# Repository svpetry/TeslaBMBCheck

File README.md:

# TeslaBMBCheck
Simple device that reads the voltage levels and temperatures from a Tesla Model S BMB board. It also supports balancing and clearing faults.

## Module Locations

## BMB Components

For each brick the BMB has a group of identical SMD components to read the voltage levels and do balancing. The elements in the topmost rectangle have already been replaced and re-sealed with epoxy.

## BMB Single Group For A Brick

The components here often have corrosion damage.

## BMB Resistor And Capacitor Values

These are the values I measured.

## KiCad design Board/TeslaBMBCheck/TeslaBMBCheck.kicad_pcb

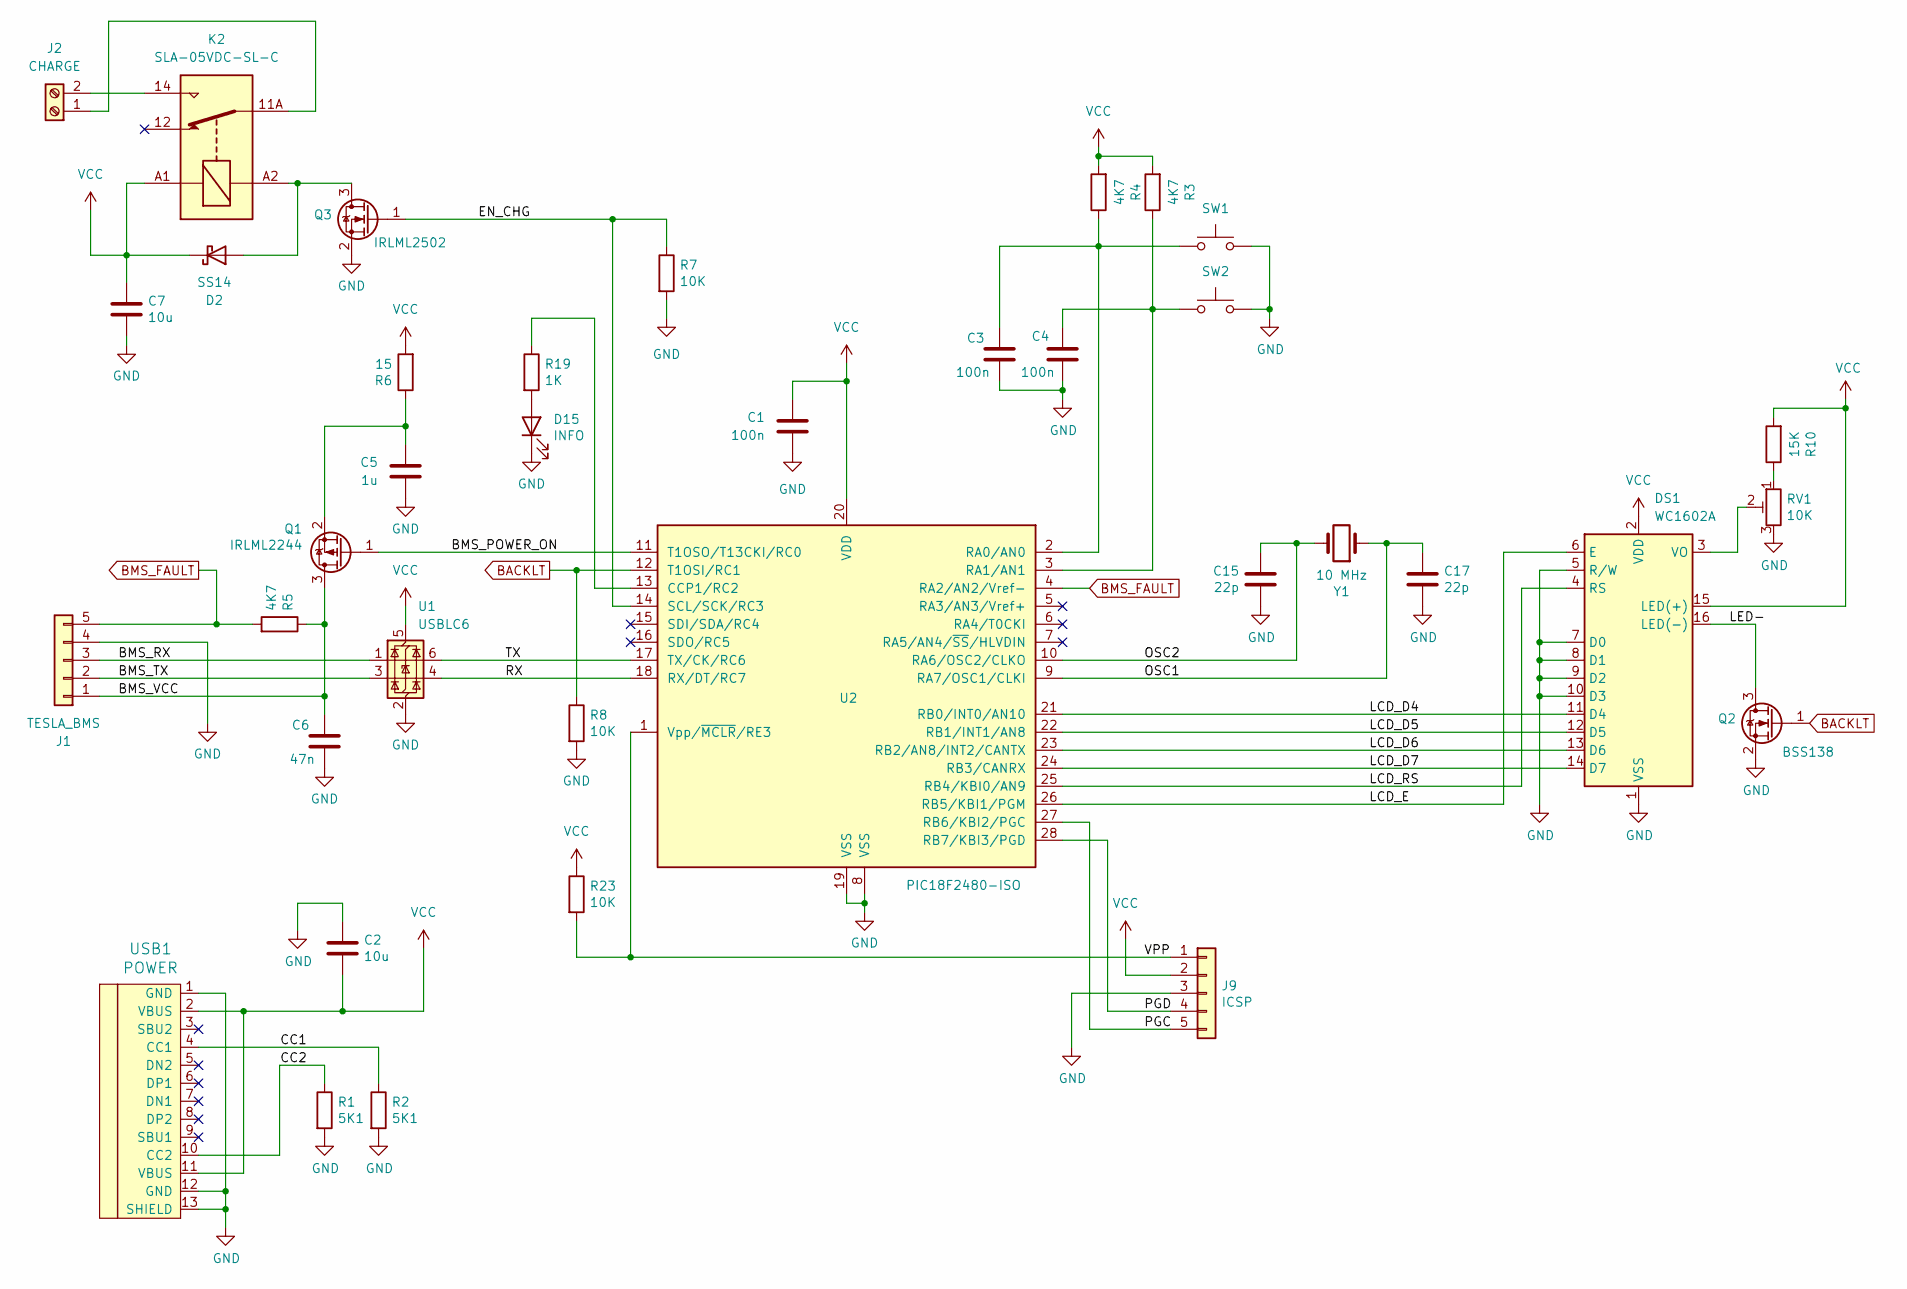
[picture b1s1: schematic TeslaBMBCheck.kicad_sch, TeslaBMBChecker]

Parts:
C1, C3, C4: 100n; C_0805_2012Metric
C2, C7: 10u; C_1206_3216Metric
C5: 1u; C_0805_2012Metric
C6: 47n; C_0805_2012Metric
C15, C17: 22p; C_0805_2012Metric
D2: SS14; D_SMA
D15: INFO; LED_0805_2012Metric
DS1: WC1602A; LCD-20x4
J1: TESLA_BMS; Molex_Mini-Fit_Jr_5566-10A_1x05_P4.20mm_Vertical
J2: CHARGE; KF7.62_2P
J9: ICSP; PinHeader_1x05_P2.54mm_Vertical
K2: SLA-05VDC-SL-C; Relay_SPDT_RAYEX-L90
Q1: IRLML2244; SOT-23
Q2: BSS138; SOT-23
Q3: IRLML2502; SOT-23
R1, R2: 5K1; R_0805_2012Metric
R3, R4, R5: 4K7; R_0805_2012Metric
R6: 15; R_0805_2012Metric
R7, R8, R23: 10K; R_0805_2012Metric
R10: 15K; R_0805_2012Metric
R19: 1K; R_0805_2012Metric
RV1: 10K; Potentiometer_Bourns_TC33X_Vertical
SW1, SW2: SW_SPST_CK_RS282G05A3
U1: USBLC6; SOT-23-6
U2: PIC18F2480-ISO; SOIC-28W_7.5x17.9mm_P1.27mm
USB1: POWER; HRO-TYPE-C-31-M-12
Y1: 10 MHz; Crystal_SMD_HC49-SD

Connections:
/BMS_POWER_ON: Q1.1 (G), U2.11 (T1OSO/T13CKI/RC0)
/BMS_RX: J1.3, U1.1 (I/O1)
/BMS_TX: J1.2, U1.3 (I/O2)
/BMS_VCC: C6.1, J1.1, Q1.3 (D), R5.1
/CC1: R2.1, USB1.4 (CC1)
/CC2: R1.1, USB1.10 (CC2)
/EN_CHG: Q3.1 (G), R7.1, U2.14 (SCL/SCK/RC3)
/LCD_D4: DS1.11 (D4), U2.21 (RB0/INT0/AN10)
/LCD_D5: DS1.12 (D5), U2.22 (RB1/INT1/AN8)
/LCD_D6: DS1.13 (D6), U2.23 (RB2/AN8/INT2/CANTX)
/LCD_D7: DS1.14 (D7), U2.24 (RB3/CANRX)
/LCD_E: DS1.6 (E), U2.26 (RB5/KBI1/PGM)
/LCD_RS: DS1.4 (RS), U2.25 (RB4/KBI0/AN9)
/LED-: DS1.16 (LED(-)), Q2.3 (D)
/OSC1: C17.1, U2.9 (RA7/OSC1/CLKI), Y1.1
/OSC2: C15.1, U2.10 (RA6/OSC2/CLKO), Y1.2
/PGC: J9.5, U2.27 (RB6/KBI2/PGC)
/PGD: J9.4, U2.28 (RB7/KBI3/PGD)
/RX: U1.4 (I/O2), U2.18 (RX/DT/RC7)
/TX: U1.6 (I/O1), U2.17 (TX/CK/RC6)
/VPP: J9.1, R23.2, U2.1 (Vpp/~MCLR/RE3)
BACKLT: Q2.1 (G), R8.1, U2.12 (T1OSI/RC1)
BMS_FAULT: J1.5, R5.2, U2.4 (RA2/AN2/Vref-)
GND: C1.2, C2.1, C3.2, C4.2, C5.2, C6.2, C7.2, C15.2, C17.2, D15.1 (K), DS1.1 (VSS), DS1.5 (R/W), DS1.7 (D0), DS1.8 (D1), DS1.9 (D2), DS1.10 (D3), J1.4, J9.3, Q2.2 (S), Q3.2 (S), R1.2, R2.2, R7.2, R8.2, RV1.3, SW1.2, SW2.2, U1.2 (GND), U2.8 (VSS), U2.19 (VSS), USB1.1 (GND), USB1.12 (GND), USB1.13 (SHIELD)
unnamed: D2.2 (A), K2.A2, Q3.3 (D)
unnamed: D15.2 (A), R19.2
unnamed: DS1.3 (VO), RV1.2
unnamed: J2.1, K2.11A, K2.11B
unnamed: J2.2, K2.14
unnamed: C5.1, Q1.2 (S), R6.1
unnamed: R10.1, RV1.1
unnamed: R19.1, U2.13 (CCP1/RC2)
unnamed: C3.1, R4.1, SW1.1, U2.2 (RA0/AN0)
unnamed: C4.1, R3.1, SW2.1, U2.3 (RA1/AN1)
VCC: C1.1, C2.2, C7.1, D2.1 (K), DS1.2 (VDD), DS1.15 (LED(+)), J9.2, K2.A1, R3.2, R4.2, R6.2, R10.2, R23.1, U1.5 (VBUS), U2.20 (VDD), USB1.2 (VBUS), USB1.11 (VBUS)

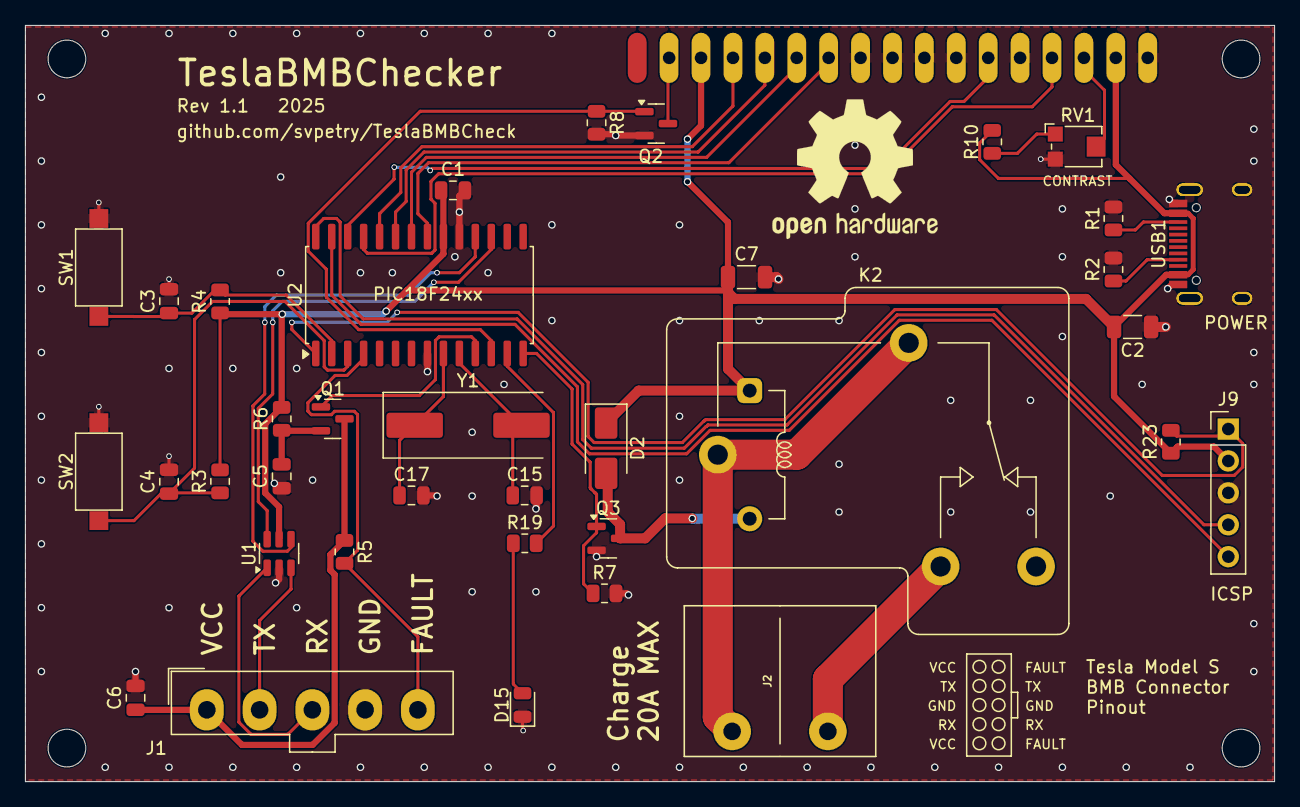
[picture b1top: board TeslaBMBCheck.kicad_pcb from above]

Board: 2 copper layers, 99.4 x 60.2 mm, 37 parts (1 on the bottom side), 35 nets.

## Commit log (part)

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2025-07-05 Initial commit (WIP)
2025-07-05 First working version.
2025-07-05 Minor fixes/improvements.
2025-07-10 Syntax fix
2025-07-10 Board & schematic
2025-07-10 Change info LED connection
2025-07-11 Layout improvements
2025-07-11 Migration to PIC18F2480. Replaces float with integer calculations. Use lookup table for temperature values.
2025-07-11 Final fixes. Created Gerber files.
2025-07-12 MCU: Add main menu, add cell balancing.
2025-07-12 MCU: Adds missing files
2025-07-13 Refactoring, minor improvements.
2025-07-14 Replaces float with integer calculcations.
2025-07-20 Refactoring. Small improvements
2025-07-24 Fixes config
2025-07-24 Minor fixes
2025-07-25 Fixed balancer
2025-07-26 Fixes, UI improvements.
2025-07-26 Fixes swapped RX/TX. Changes R10 value
2025-07-27 Adds fault detection and clearing.
2025-07-27 Refactoring. Adds battery symbols. Adds warning sign for faults.
2025-08-02 Add images. Remove stuff.
2025-08-16 Small fixes. Remove KiCad warnings.
2025-08-30 Minor fixes. Clear faults on connect.
2025-08-30 Adds images
2025-09-25 Minor improvements
2025-09-26 Adds charging relais. New layout.
2025-09-26 Minor layout changes
2025-09-26 Adds 1.1 gerber files.
2025-10-07 Changes for PIC18F2455
2025-10-09 Changes for PIC18F2420
2025-10-11 Implemented charging mode
2025-10-11 Fixed charging. Change firmware revision to 1.1
